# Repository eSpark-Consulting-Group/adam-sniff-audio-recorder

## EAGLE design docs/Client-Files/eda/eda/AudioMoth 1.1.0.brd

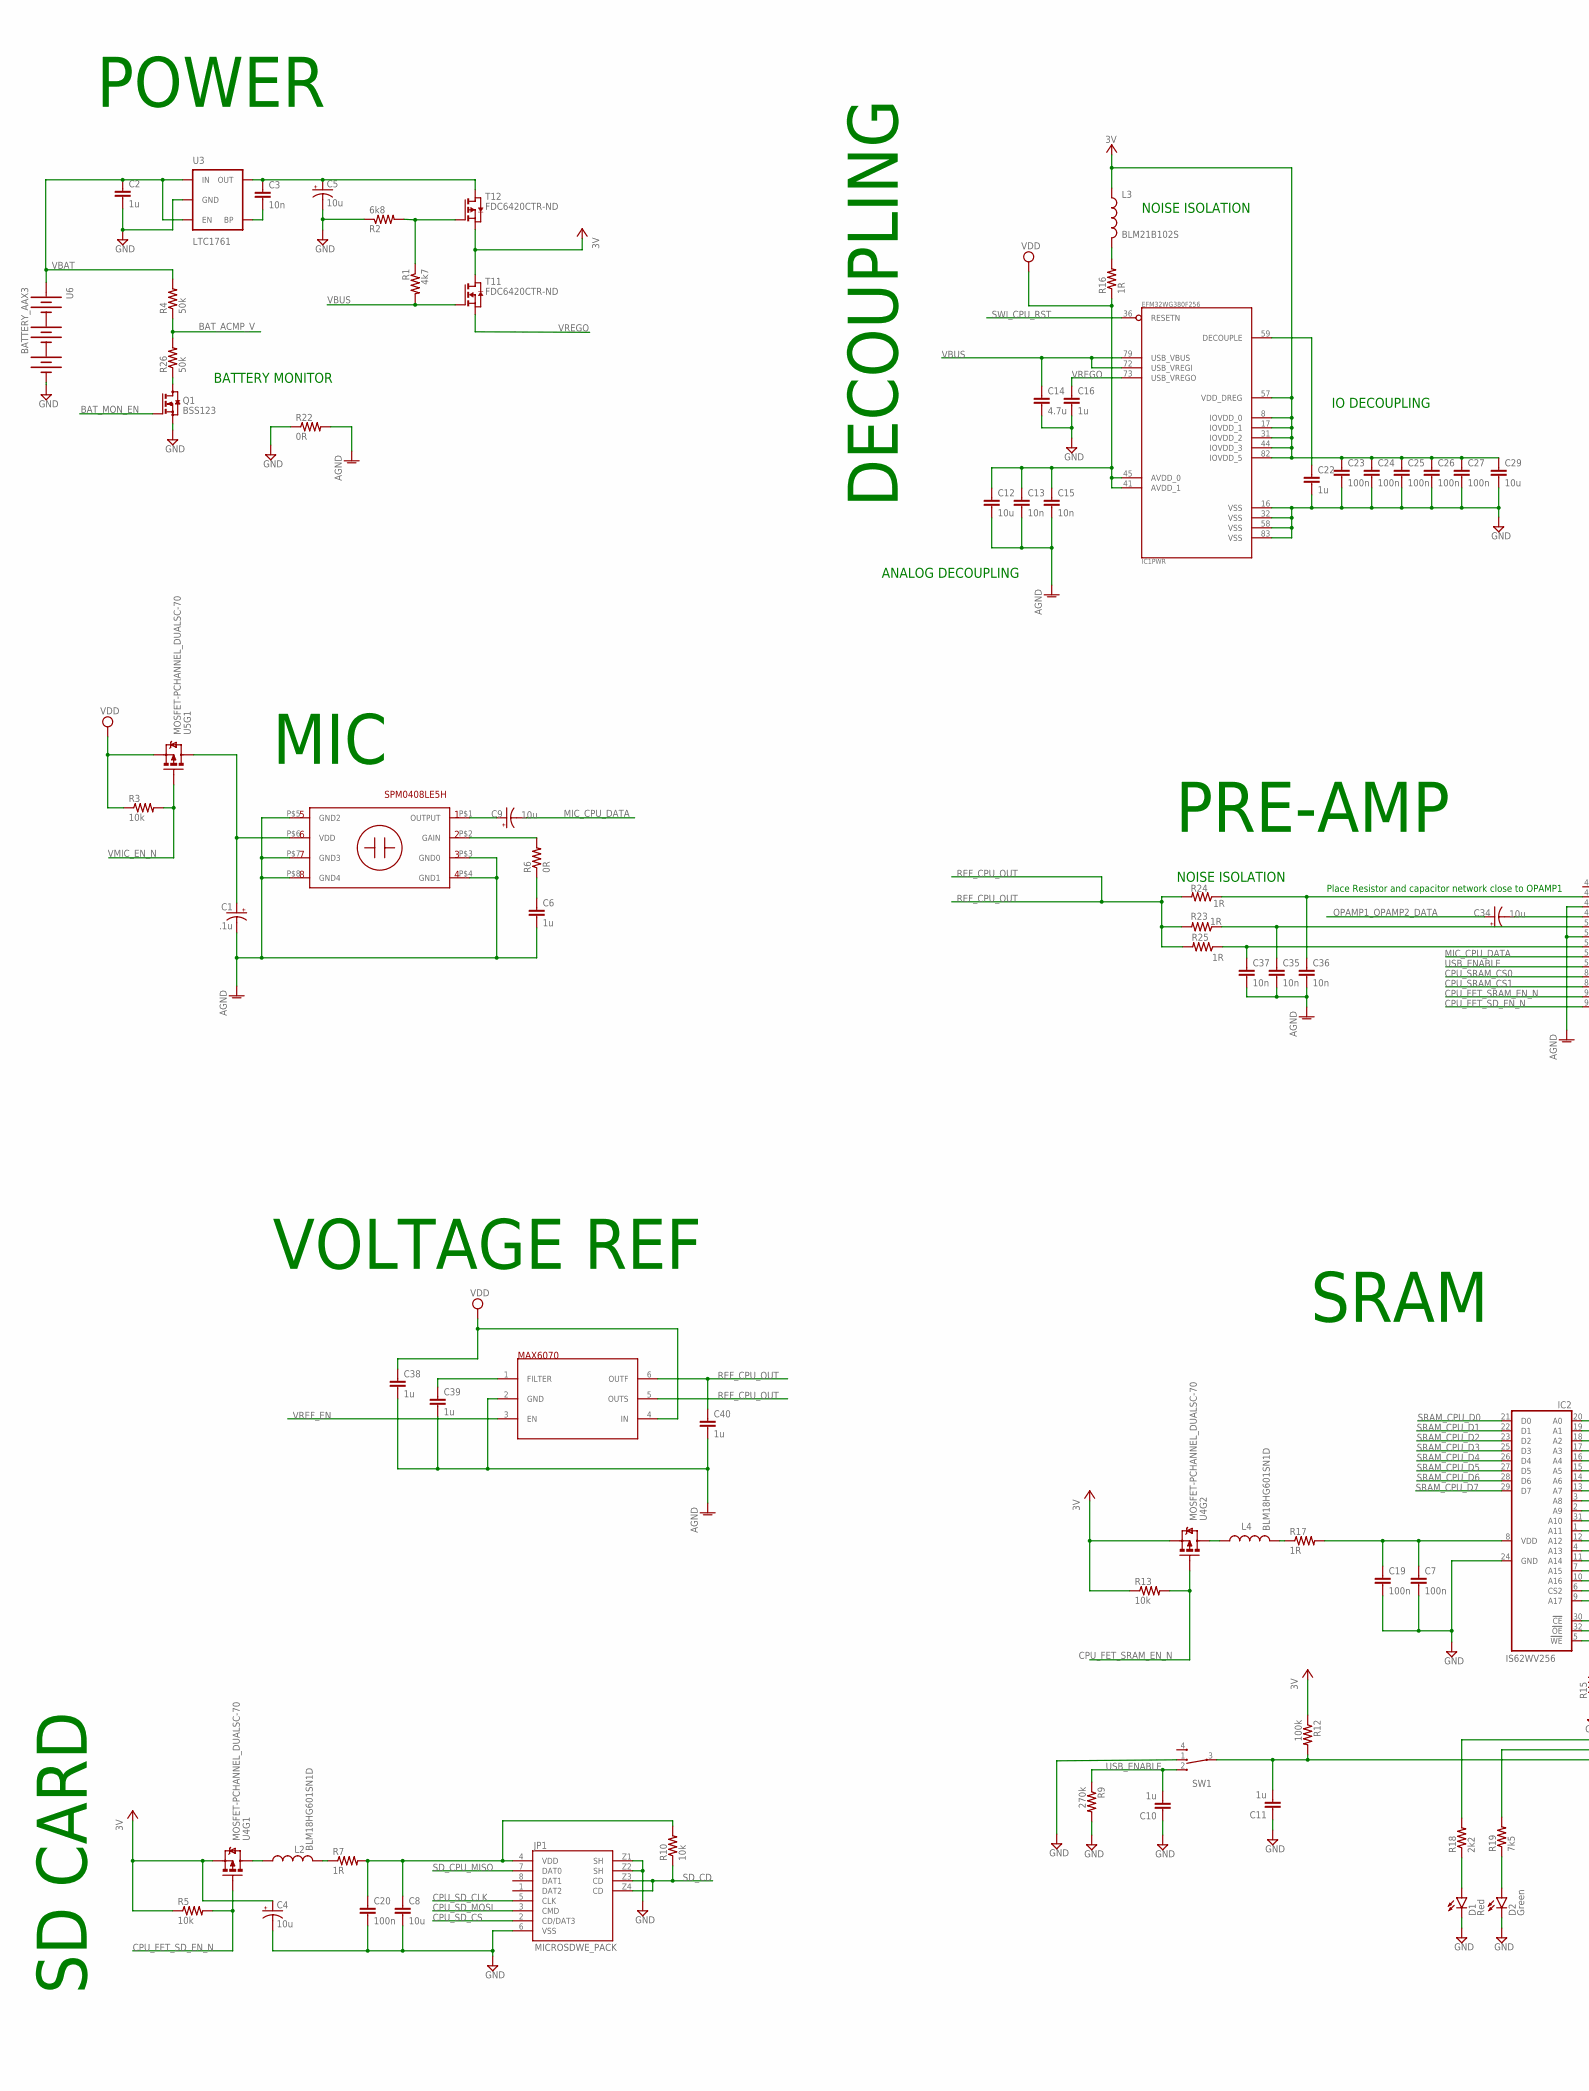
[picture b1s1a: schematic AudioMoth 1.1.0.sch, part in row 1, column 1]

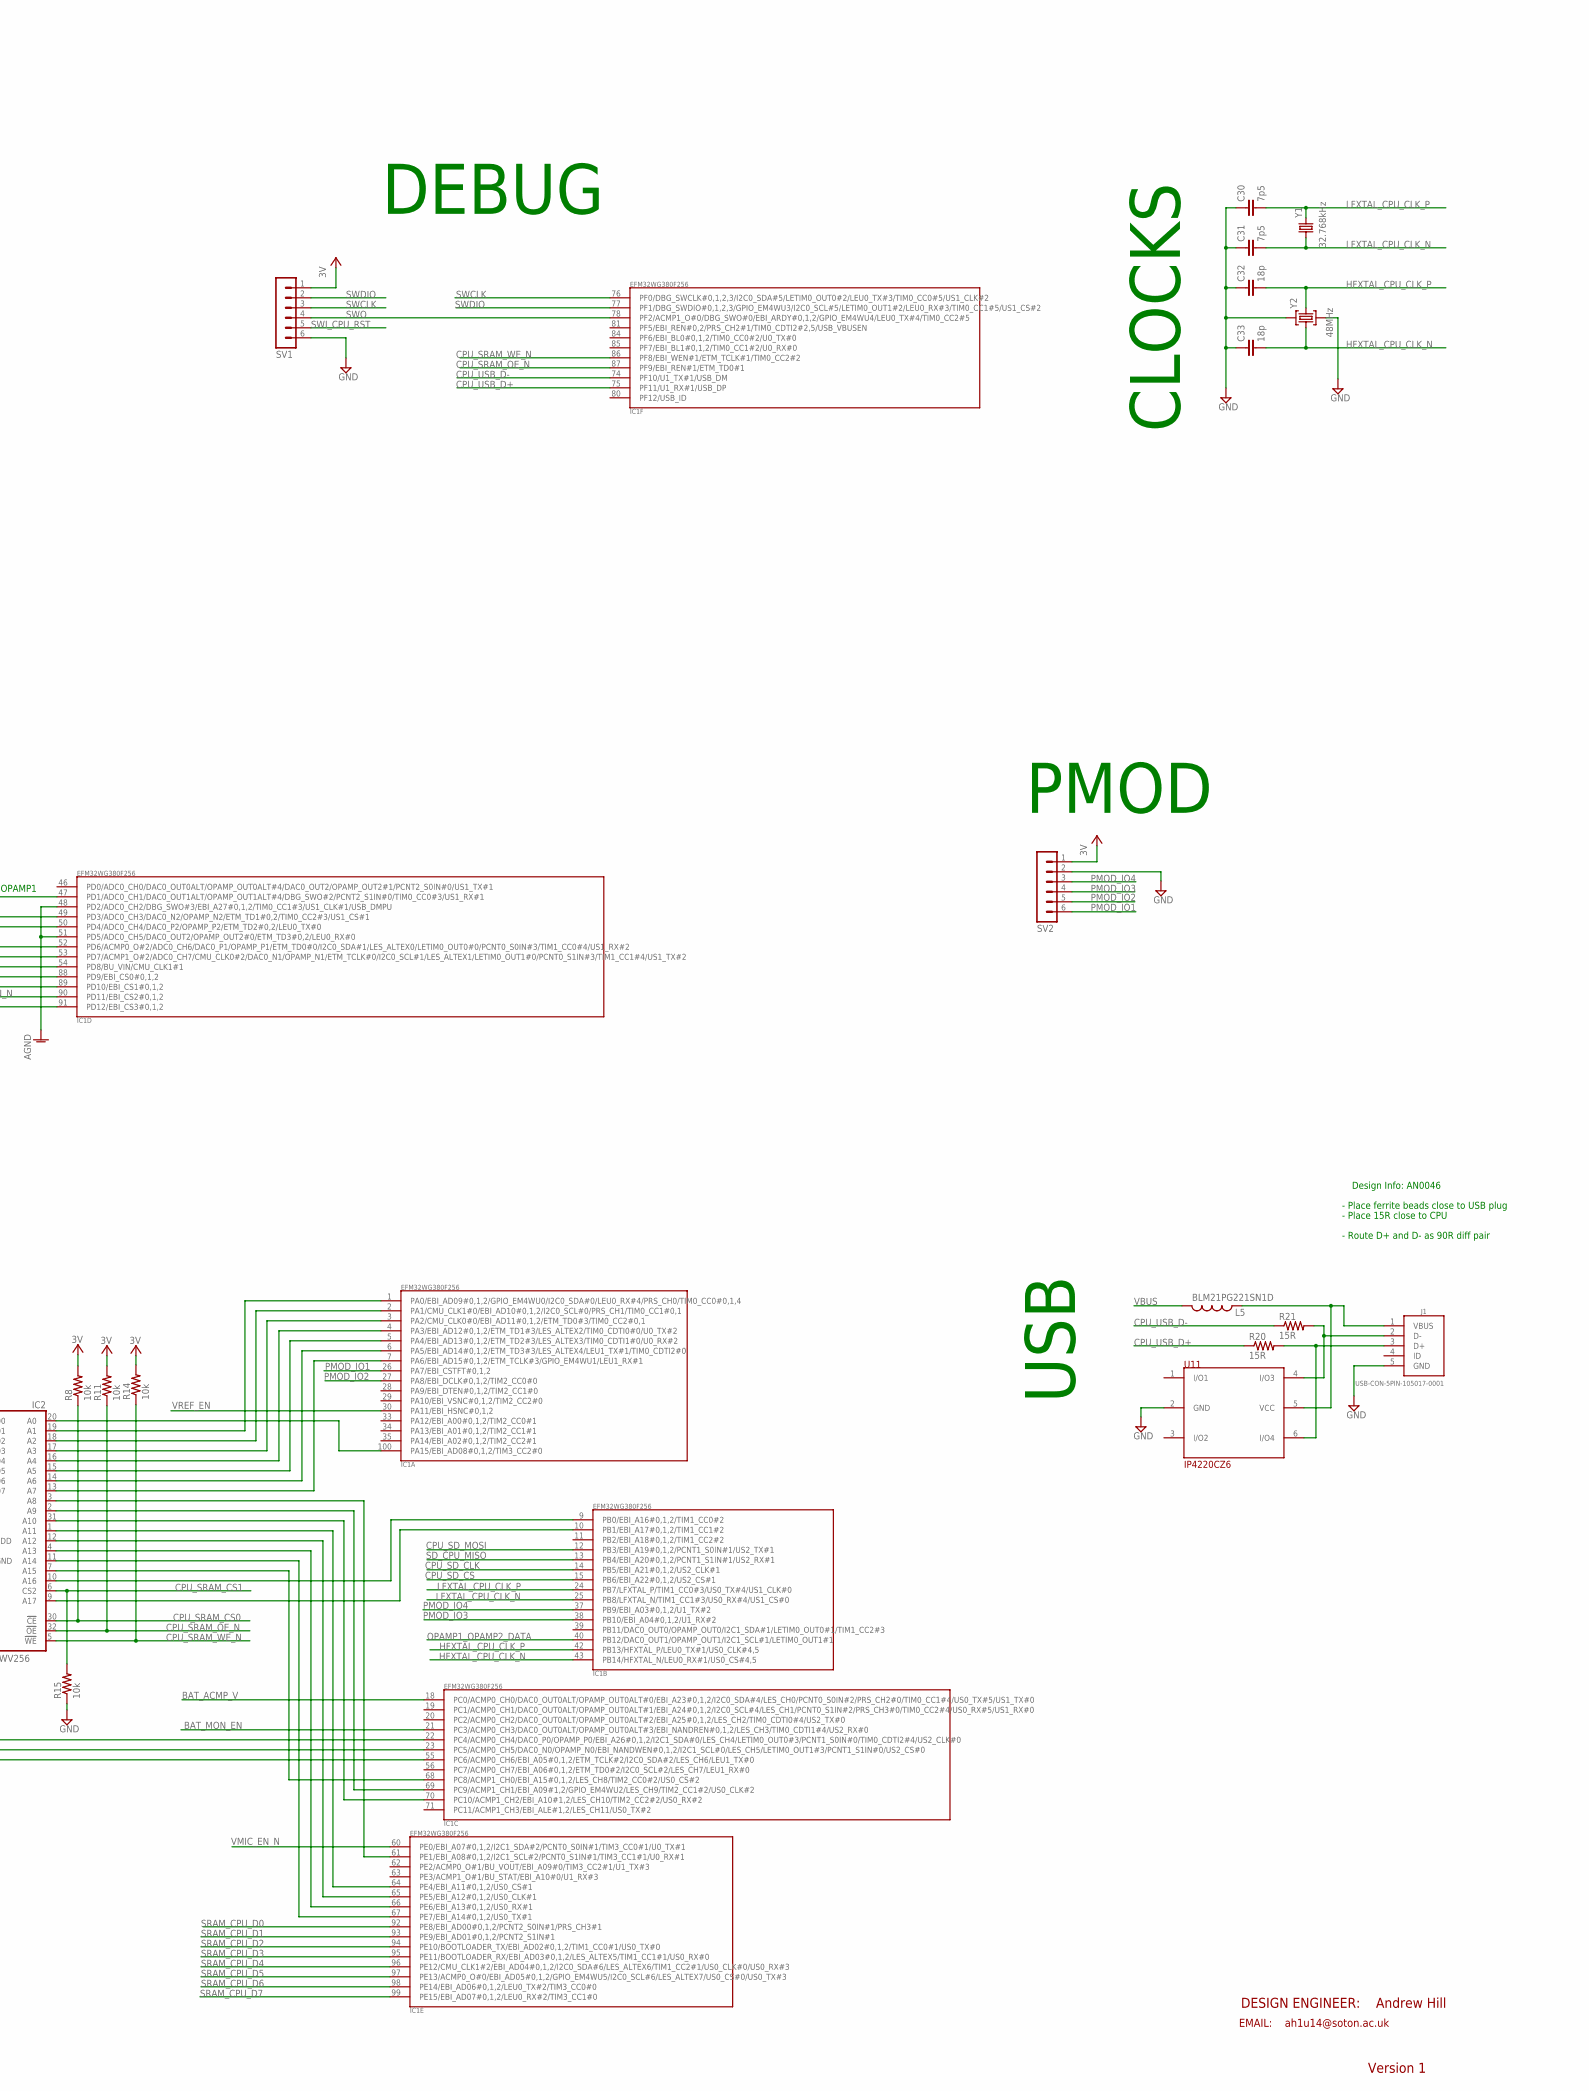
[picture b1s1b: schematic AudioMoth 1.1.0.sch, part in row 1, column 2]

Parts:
C1: .1u; EIA3216-KIT; MPN 293D106X96R3A2TE3
C2, C6, C10, C11, C16, C22: 1u; 0402
C3, C13, C15: 10n; 0402
C4, C5, C9, C34: 10u; EIA3216-KIT; MPN 0603ZD106MAT2A
C7, C19, C20, C23, C24, C25, C26, C27: 100n; 0402
C8, C29: 10u; C0603; MPN 0603ZD106MAT2A
C12: 10u; 0603-CAP; MPN 0603ZD106MAT2A
C14: 4.7u; 0402
C30, C31: 7p5; 0402
C32, C33: 18p; 0402
C35, C36, C37: 10n; 0402; MPN 0603B103K250CT
C38, C39, C40: 1u; 0402; MPN MC0603F105Z100CT
D1: Red; LED-0603
D2: Green; LED-0603
IC1: EFM32WG380F256; QFP100
IC2: IS62WV256
J1: USB-CON-5PIN-105017-0001; USB-MICRO-MOLEX-105017-0001
JP1: MICROSDWE_PACK; 693071010811; MPN 693071010811
L2, L4: BLM18HG601SN1D; 0603-RES
L3: BLM21B102S; 0805
L5: BLM21PG221SN1D; 0603-RES
Q1: BSS123; SOT23
R1: 4k7; 0402
R2: 6k8; 0402
R3, R5, R8, R10, R11, R13, R14, R15: 10k; 0402
R4, R26: 50k; 0402
R6: 0R; 0402
R7, R16, R17: 1R; 0402
R9: 270k; 0402
R12: 100k; 0402
R18: 2k2; 0402
R19: 7k5; 0402
R20, R21: 15R; 0402
R22: 0R; 0603-RES
R23, R24, R25: 1R; 0402; MPN MC0063W0603510K
SV1, SV2: MA06-1SMD_BOARD_EDGE; TSM-106-X-SH-BOARDEDGE
SW1: CT10-XXXX-CSS131; CT10-XXXX-G4
T1: FDC6420CTR-ND; SOT23-6
U1: MAX6070SOT23; SOT26@1
U2: SPM0408LE5H; SPM0408LE5H-TB
U3: LTC1761; SOT23-5; MPN LT1761ES5-3.3#TRMPBF
U4, U5: MOSFET-PCHANNEL_DUALSC-70; SC-70
U6: BATTERY_AAX3; BATTERY-AAX3
U11: IP4220CZ6; SC-74
Y1: 32.768kHz; CRYSTAL-32KHZ-SMD_EPSON_MC146; MPN X32K768S019
Y2: 48MHz; XRCGB48M000F4M00R0; MPN ABM3B-12.000MHZ-B2-T

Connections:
+3V3: C4.A (+), C23.1, C24.1, C25.1, C26.1, C27.1, C29.1, IC1.8 (IOVDD_0), IC1.17 (IOVDD_1), IC1.31 (IOVDD_2), IC1.44 (IOVDD_3), IC1.57 (VDD_DREG), IC1.82 (IOVDD_5), L3.1, R5.1, R8.2, R11.2, R12.1, R13.1, R14.2, SV1.1, SV2.1, T1.2 (S), T1.6 (D), U4.1 (S), U4.4 (S)
AGND: C1.C (-), C6.2, C12.2, C13.2, C15.2, C35.2, C36.2, C37.2, C38.2, C39.2, C40.2, IC1.48 (PD2/ADC0_CH2/DBG_SWO#3/EBI_A27#0,1,2/TI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), IC1.51 (PD5/ADC0_CH5/DAC0_OUT2/OPAMP_OUT2#0/ETM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), R22.2, U1.2 (GND), U2.P$3 (GND0), U2.P$4 (GND1), U2.P$5 (GND2), U2.P$7 (GND3), U2.P$8 (GND4)
BAT_ACMP_V: IC1.18 (PC0/ACMP0_CH0/DAC0_OUT0ALT/OPAMP_OUT0AL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), R4.1, R26.2
BAT_MON_EN: IC1.21 (PC3/ACMP0_CH3/DAC0_OUT0ALT/OPAMP_OUT0AL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), Q1.1 (G)
CPU_FET_SD_EN_N: IC1.91 (PD12/EBI_CS3#0,1,2), R5.2, U4.2 (G)
CPU_FET_SRAM_EN_N: IC1.90 (PD11/EBI_CS2#0,1,2), R13.2, U4.5 (G)
CPU_SD_CLK: IC1.14 (PB5/EBI_A21#0,1,2/US2_CLK#1), JP1.5 (CLK)
CPU_SD_CS: IC1.15 (PB6/EBI_A22#0,1,2/US2_CS#1), JP1.2 (CD/DAT3)
CPU_SD_MOSI: IC1.12 (PB3/EBI_A19#0,1,2/PCNT1_S0IN#1/US2_TX#1), JP1.3 (CMD)
CPU_SRAM_CS0: IC1.88 (PD9/EBI_CS0#0,1,2), IC2.30 (!CE), R8.1
CPU_SRAM_CS1: IC1.89 (PD10/EBI_CS1#0,1,2), IC2.6 (CS2), R15.2
CPU_SRAM_OE_N: IC1.87 (PF9/EBI_REN#1/ETM_TD0#1), IC2.32 (!OE), R11.1
CPU_SRAM_WE_N: IC1.86 (PF8/EBI_WEN#1/ETM_TCLK#1/TIM0_CC2#2), IC2.5 (!WE), R14.1
CPU_USB_D+: IC1.75 (PF11/U1_RX#1/USB_DP), R20.1
CPU_USB_D-: IC1.74 (PF10/U1_TX#1/USB_DM), R21.1
GND: C2.2, C4.C (-), C5.C (-), C7.2, C8.2, C10.1, C11.1, C14.2, C16.2, C19.2, C20.2, C22.2, C23.2, C24.2, C25.2, C26.2, C27.2, C29.2, C30.1, C31.1, C32.1, C33.1, D1.C, D2.C, IC1.16 (VSS), IC1.32 (VSS), IC1.58 (VSS), IC1.83 (VSS), IC2.24 (GND), J1.5 (GND), JP1.6 (VSS), JP1.Z1 (SH), JP1.Z2 (SH), Q1.2 (S), R2.1, R9.2, R15.1, R22.1, SV1.6, SV2.2, SW1.1, U3.2 (GND), U6.GND@2 (-), U11.2 (GND), Y2.P$2 (2), Y2.P$4 (4)
HFXTAL_CPU_CLK_N: C33.2, IC1.43 (PB14/HFXTAL_N/LEU0_RX#1/US0_CS#4,5), Y2.P$3 (3)
HFXTAL_CPU_CLK_P: C32.2, IC1.42 (PB13/HFXTAL_P/LEU0_TX#1/US0_CLK#4,5), Y2.P$1 (1)
LFXTAL_CPU_CLK_N: C31.2, IC1.25 (PB8/LFXTAL_N/TIM1_CC1#3/US0_RX#4/US1_CS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), Y1.P$2 (1)
LFXTAL_CPU_CLK_P: C30.2, IC1.24 (PB7/LFXTAL_P/TIM1_CC0#3/US0_TX#4/US1_CL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), Y1.P$1 (2)
MIC_CPU_DATA: C9.C (-), IC1.53 (PD7/ACMP1_O#2/ADC0_CH7/CMU_CLK0#2/DAC0_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)
unnamed: L3.2, R16.2
unnamed: C22.1, IC1.59 (DECOUPLE)
unnamed: C8.1, C20.1, JP1.4 (VDD), R7.2, R10.2
unnamed: C34.C (-), IC1.49 (PD3/ADC0_CH3/DAC0_N2/OPAMP_N2/ETM_TD1#0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)
unnamed: L2.2, R7.1
unnamed: L2.1, U4.6 (D)
unnamed: C9.A (+), U2.P$1 (OUTPUT)
unnamed: Q1.3 (D), R26.1
unnamed: C11.2, IC1.55 (PC6/ACMP0_CH6/EBI_A05#0,1,2/ETM_TCLK#2/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), R12.2, SW1.3
unnamed: C3.1, C5.A (+), T1.4 (D), U3.5 (OUT)
unnamed: D2.A, R19.1
unnamed: D1.A, R18.1
unnamed: IC1.23 (PC5/ACMP0_CH5/DAC0_N0/OPAMP_N0/EBI_NAND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), R19.2
unnamed: IC1.22 (PC4/ACMP0_CH4/DAC0_P0/OPAMP_P0/EBI_A26#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), R18.2
unnamed: J1.1 (VBUS), L5.1, U11.5 (VCC)
unnamed: C3.2, U3.4 (BP)
unnamed: IC1.100 (PA15/EBI_AD08#0,1,2/TIM3_CC2#0), IC2.20 (A0)
unnamed: IC1.1 (PA0/EBI_AD09#0,1,2/GPIO_EM4WU0/I2C0_SDA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), IC2.19 (A1)
unnamed: J1.2 (D-), R21.2, U11.4 (I/O3)
unnamed: IC1.2 (PA1/CMU_CLK1#0/EBI_AD10#0,1,2/I2C0_SCL#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), IC2.18 (A2)
unnamed: IC1.3 (PA2/CMU_CLK0#0/EBI_AD11#0,1,2/ETM_TD0#3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), IC2.17 (A3)
unnamed: J1.3 (D+), R20.2, U11.6 (I/O4)
unnamed: R6.2, U2.P$2 (GAIN)
unnamed: C6.1, R6.1
unnamed: IC1.4 (PA3/EBI_AD12#0,1,2/ETM_TD1#3/LES_ALTEX2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), IC2.16 (A4)
unnamed: IC1.5 (PA4/EBI_AD13#0,1,2/ETM_TD2#3/LES_ALTEX3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), IC2.15 (A5)
unnamed: IC1.6 (PA5/EBI_AD14#0,1,2/ETM_TD3#3/LES_ALTEX4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), IC2.14 (A6)
unnamed: IC1.7 (PA6/EBI_AD15#0,1,2/ETM_TCLK#3/GPIO_EM4W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), IC2.13 (A7)
unnamed: IC1.61 (PE1/EBI_A08#0,1,2/I2C1_SCL#2/PCNT0_S1IN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), IC2.3 (A8)
unnamed: IC1.69 (PC9/ACMP1_CH1/EBI_A09#1,2/GPIO_EM4WU2/L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), IC2.2 (A9)
unnamed: IC1.70 (PC10/ACMP1_CH2/EBI_A10#1,2/LES_CH10/TIM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), IC2.31 (A10)
unnamed: L4.1, U4.3 (D)
unnamed: IC1.64 (PE4/EBI_A11#0,1,2/US0_CS#1), IC2.1 (A11)
unnamed: IC1.65 (PE5/EBI_A12#0,1,2/US0_CLK#1), IC2.12 (A12)
unnamed: IC1.66 (PE6/EBI_A13#0,1,2/US0_RX#1), IC2.4 (A13)
unnamed: IC1.67 (PE7/EBI_A14#0,1,2/US0_TX#1), IC2.11 (A14)
unnamed: IC1.68 (PC8/ACMP1_CH0/EBI_A15#0,1,2/LES_CH8/TIM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), IC2.7 (A15)
unnamed: IC1.9 (PB0/EBI_A16#0,1,2/TIM1_CC0#2), IC2.10 (A16)
unnamed: IC1.10 (PB1/EBI_A17#0,1,2/TIM1_CC1#2), IC2.9 (A17)
unnamed: C35.1, IC1.50 (PD4/ADC0_CH4/DAC0_P2/OPAMP_P2/ETM_TD2#0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), R23.1
unnamed: C7.1, C19.1, IC2.8 (VDD), R17.2
unnamed: C36.1, IC1.47 (PD1/ADC0_CH1/DAC0_OUT1ALT/OPAMP_OUT1ALT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), R24.1
unnamed: L4.2, R17.1
unnamed: C37.1, IC1.52 (PD6/ACMP0_O#2/ADC0_CH6/DAC0_P1/OPAMP_P1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), R25.1
unnamed: C39.1, U1.1 (FILTER)
unnamed: R1.1, R2.2, T1.3 (G)
OPAMP1_OPAMP2_DATA: C34.A (+), IC1.40 (PB12/DAC0_OUT1/OPAMP_OUT1/I2C1_SCL#1/LE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)
PMOD_IO1: IC1.26 (PA7/EBI_CSTFT#0,1,2), SV2.6
PMOD_IO2: IC1.27 (PA8/EBI_DCLK#0,1,2/TIM2_CC0#0), SV2.5
PMOD_IO3: IC1.38 (PB10/EBI_A04#0,1,2/U1_RX#2), SV2.4
PMOD_IO4: IC1.37 (PB9/EBI_A03#0,1,2/U1_TX#2), SV2.3
REF_CPU_OUT: C40.1, R23.2, R24.2, R25.2, U1.5 (OUTS), U1.6 (OUTF)
SD_CD: JP1.Z3 (CD), JP1.Z4 (CD), R10.1
SD_CPU_MISO: IC1.13 (PB4/EBI_A20#0,1,2/PCNT1_S1IN#1/US2_RX#1), JP1.7 (DAT0)
SRAM_CPU_D0: IC1.92 (PE8/EBI_AD00#0,1,2/PCNT2_S0IN#1/PRS_CH3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), IC2.21 (D0)
SRAM_CPU_D1: IC1.93 (PE9/EBI_AD01#0,1,2/PCNT2_S1IN#1), IC2.22 (D1)
SRAM_CPU_D2: IC1.94 (PE10/BOOTLOADER_TX/EBI_AD02#0,1,2/TIM1_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), IC2.23 (D2)
SRAM_CPU_D3: IC1.95 (PE11/BOOTLOADER_RX/EBI_AD03#0,1,2/LES_A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), IC2.25 (D3)
SRAM_CPU_D4: IC1.96 (PE12/CMU_CLK1#2/EBI_AD04#0,1,2/I2C0_SDA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), IC2.26 (D4)
SRAM_CPU_D5: IC1.97 (PE13/ACMP0_O#0/EBI_AD05#0,1,2/GPIO_EM4W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), IC2.27 (D5)
SRAM_CPU_D6: IC1.98 (PE14/EBI_AD06#0,1,2/LEU0_TX#2/TIM3_CC0#0), IC2.28 (D6)
SRAM_CPU_D7: IC1.99 (PE15/EBI_AD07#0,1,2/LEU0_RX#2/TIM3_CC1#0), IC2.29 (D7)
SWCLK: IC1.76 (PF0/DBG_SWCLK#0,1,2,3/I2C0_SDA#5/LETIM0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), SV1.3
SWDIO: IC1.77 (PF1/DBG_SWDIO#0,1,2,3/GPIO_EM4WU3/I2C0_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), SV1.2
SWI_CPU_RST: IC1.36 (RESETN), SV1.5
SWO: IC1.78 (PF2/ACMP1_O#0/DBG_SWO#0/EBI_ARDY#0,1,2/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), SV1.4
USB_ENABLE: C10.2, IC1.54 (PD8/BU_VIN/CMU_CLK1#1), R9.1, SW1.2
VAMP: C1.A (+), U2.P$6 (VDD), U5.6 (D)
VBAT: C2.1, R4.2, U3.1 (IN), U3.3 (EN), U6.PWR@1 (+)
VBUS: C14.1, IC1.72 (USB_VREGI), IC1.79 (USB_VBUS), L5.2, R1.2, T1.1 (G)
VDD: C12.1, C13.1, C15.1, C38.1, IC1.41 (AVDD_1), IC1.45 (AVDD_0), R3.1, R16.1, U1.4 (IN), U5.1 (S)
VMIC_EN_N: IC1.60 (PE0/EBI_A07#0,1,2/I2C1_SDA#2/PCNT0_S0IN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), R3.2, U5.2 (G)
VREF_EN: IC1.30 (PA11/EBI_HSNC#0,1,2), U1.3 (EN)
VREGO: C16.1, IC1.73 (USB_VREGO), T1.5 (S)

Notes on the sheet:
DEBUG
POWER
IO DECOUPLING
NOISE ISOLATION
USB
SD CARD
ANALOG DECOUPLING
MIC
CLOCKS
Design Info: AN0046
- Place ferrite beads close to USB plug
- Place 15R close to CPU
- Route D+ and D- as 90R diff pair
DECOUPLING
DESIGN ENGINEER: Andrew Hill
EMAIL: ah1u14@soton.ac.uk
Version 1
PRE-AMP
SPM0408LE5H
SRAM
Place Resistor and capacitor network close to OPAMP1
VOLTAGE REF
PMOD
IS62WV256
BATTERY MONITOR

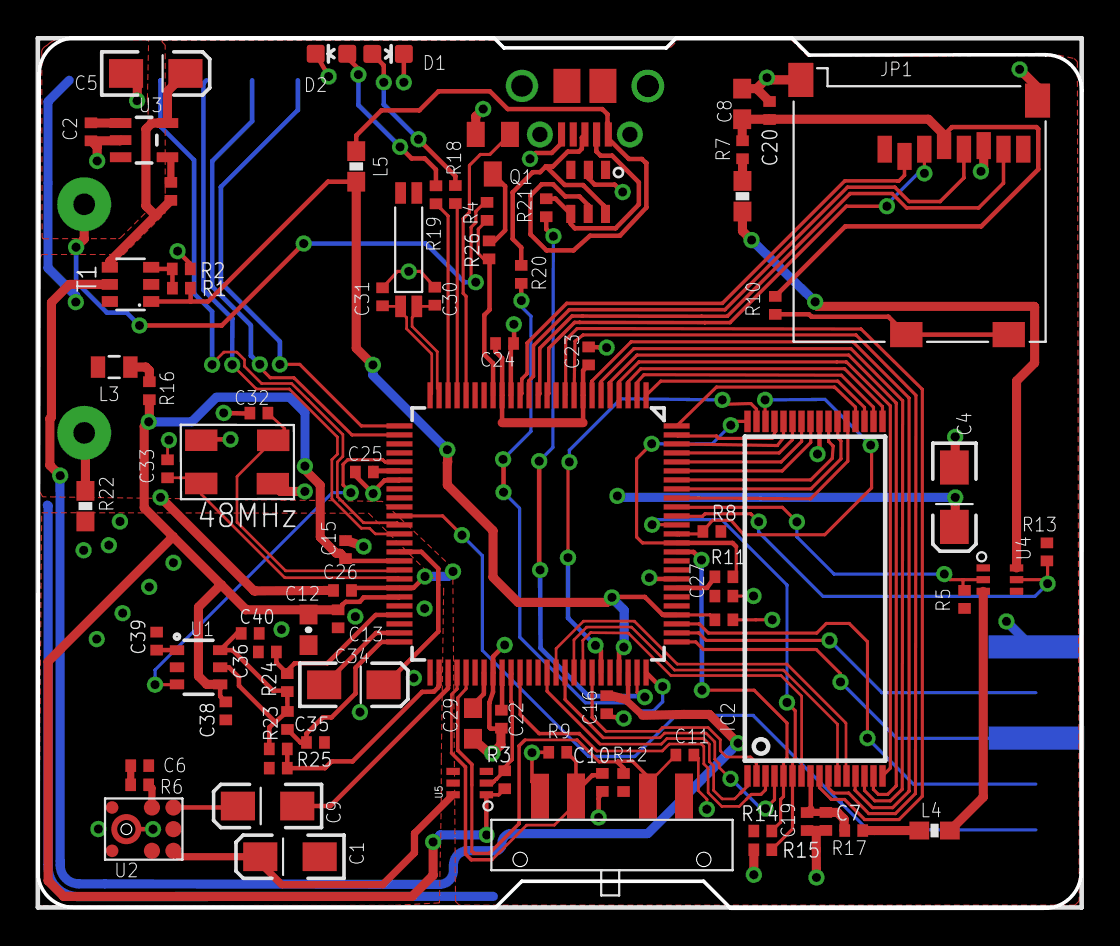
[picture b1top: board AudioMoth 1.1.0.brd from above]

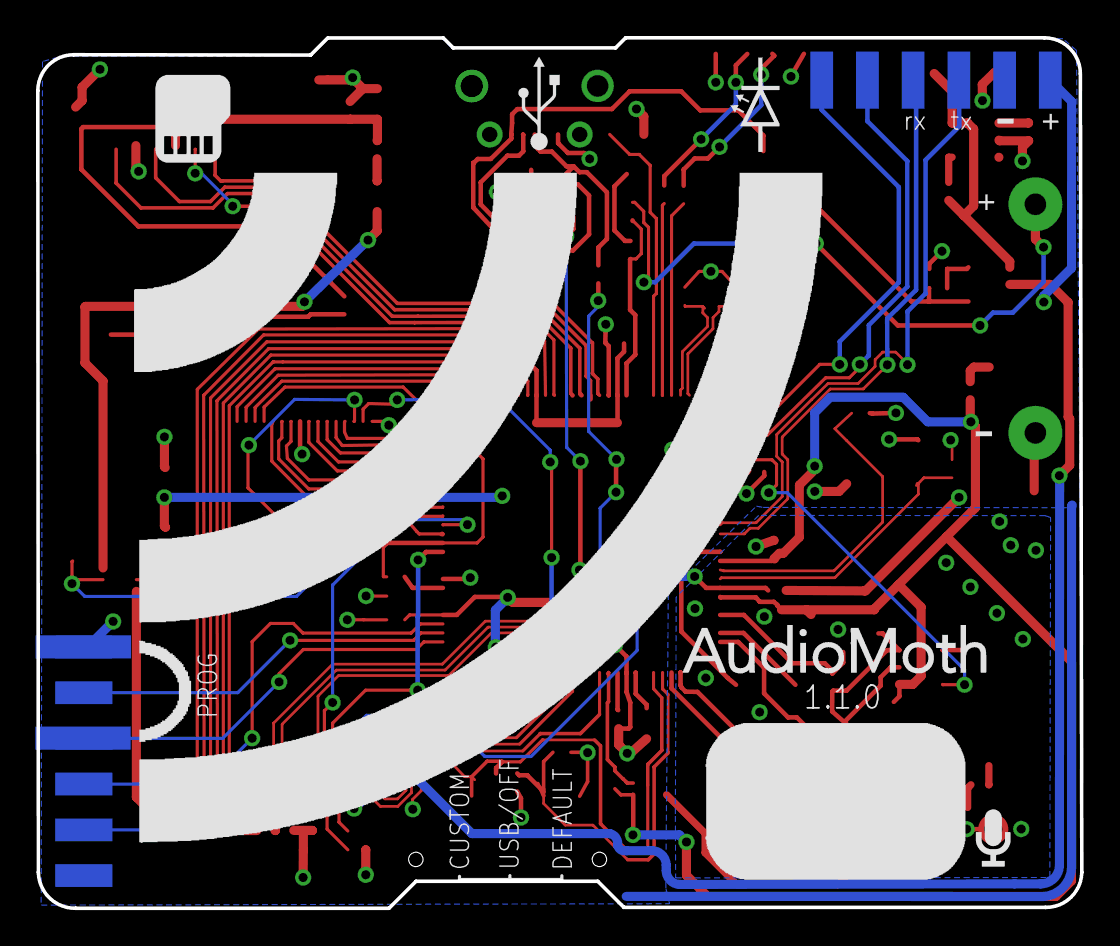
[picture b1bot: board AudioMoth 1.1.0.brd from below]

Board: 2 copper layers, 58.0 x 48.4 mm, 86 parts (2 on the bottom side), 95 nets.

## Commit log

2024-10-01 Client files pushed
2024-10-02 Eagle files pushed
2024-10-02 #1 MCU Sheet in progress
2024-10-03 #1 Ten (10) SD cards provision remaining. Other is complete
2024-10-04 #1 Complete.
2024-10-15 #1 Changed in the git issue done.
2024-10-15 #1 Version update to v1.1.0
2024-10-17 #1 LDO changed. PDF Updated
2024-10-21 #1 Version update to v1.2.0
2024-10-24 #2 Placement in Progress.
2024-10-30 #2 Placement in Progress
2024-11-05 #2 Placement completed
2024-11-06 #2 Routing in progress
2024-11-07 #2 JLC BOM added
2024-11-07 #2 BOM name updated
2024-11-11 #1 differential directives added for usb pair #2 Routing in Progress
2024-11-12 #2 length tuning in progress
2024-11-13 #2 Routing completed BOM and Deliverables generated too
2024-11-17 #3 Changes done and Deliverables generated
2024-11-18 #3 #2 Made some changes. Deliverables generated
2024-11-18 #3 BOM version number added
2024-11-19 @faizi968 Centroid File update.
    These Designators R2,R13,R8,J2,J4 Remove from Centroid.
2024-11-19 Gerber files .zip (extra) removed
2025-06-25 #5 Design Changes Complete
2025-06-25 #5 PDF generated. Old deliverables removed.
2025-06-25 #5 project file update
2025-06-25 #7 MIC board design complete.
2025-06-25 #6 In progress
2025-06-26 #6 Completed and Deliverables generated
2025-06-27 #8 PCB Completed and Deliverables generated

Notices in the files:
parts and their libraries:
SparkFun-Passives: Licensing: Creative Commons ShareAlike 4.0 International - https://creativecommons.org/licenses/by-sa/4.0
EFM32: CC0 License
